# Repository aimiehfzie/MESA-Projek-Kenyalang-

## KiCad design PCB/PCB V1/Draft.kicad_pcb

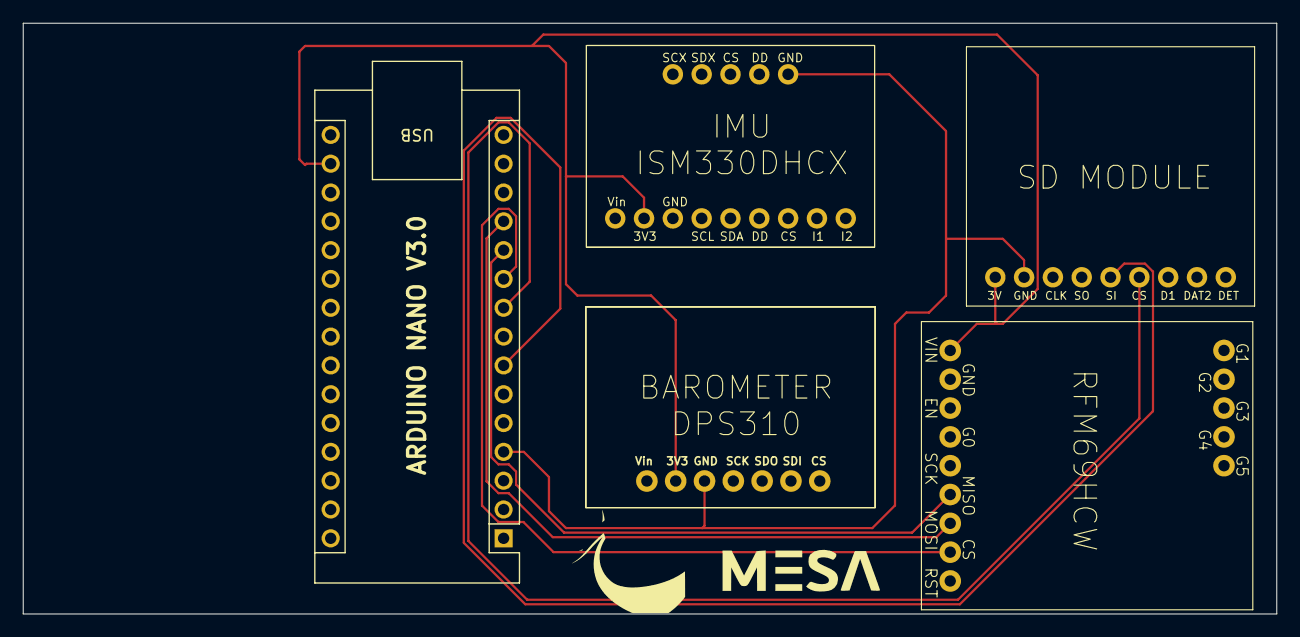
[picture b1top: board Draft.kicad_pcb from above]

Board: 2 copper layers, 110.5 x 52.1 mm, 5 parts (0 on the bottom side), 9 nets.

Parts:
A1: Arduino_Nano_v3.x; Arduino_Nano
U1: DPS310
U2: ISM330DHCX
U3: RFM69HCW Adafruit
U4: ADAFRUIT MICROSD

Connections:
GND: A1.4 (GND), U1.3 (GND), U2.6 (GND), U4.2 (GND)
unnamed: A1.17 (3V3), U1.2 (3V3), U2.8 (VDD), U3.1 (Vin), U4.1 (3V)
unnamed: A1.1 (D1/TX), A1.2 (D0/RX), U1.4 (SCK), U1.6 (SDI), U2.13 (SCL), U2.14 (SDA), U3.5 (SCK)
unnamed: A1.6 (D3), U4.4 (SO)
unnamed: A1.7 (D4), U4.5 (SI)
unnamed: A1.9 (D6), U4.6 (CS)
unnamed: A1.10 (D7), U3.8 (CS)
unnamed: A1.11 (D8), U3.6 (MISO)
unnamed: A1.12 (D9), U3.7 (MOSI)

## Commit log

2025-12-02 Create ss
2025-12-02 Rename Draft.kicad_prl to draftpcb/Draft.kicad_prl
2025-12-02 Rename Draft.kicad_pro to draftpcb/Draft.kicad_pro
2025-12-02 Rename Draft.step to draftpcb/Draft.step
2025-12-02 Rename fp-info-cache to draftpcb/fp-info-cache
2025-12-02 Update and rename fp-lib-table to draftpcb/fp-lib-table
2025-12-02 Update and rename sym-lib-table to draftpcb/sym-lib-table
2025-12-07 Create 111
2026-02-20 Create SD CARD
2026-03-16 Add README file to project
2026-03-16 Add OLED display setup for ESP32-S3
2026-04-11 Add sensor initialization and data logging code
    This file initializes various sensors and sets up an OLED display and SD card logging for data collection.
2026-04-13 Add Component Readiness Test for various sensors
2026-06-15 Add Projek_Kenyalang app for atmospheric analysis
2026-06-15 Rename Data Profililing to Data Profiling
2026-06-15 Update Final Code
2026-06-16 Implement dynamic altitude calibration and UI updates
    Added dynamic ground level calibration and updated UI components for peak altitude display.
2026-06-16 Fix missing newline at end of file
